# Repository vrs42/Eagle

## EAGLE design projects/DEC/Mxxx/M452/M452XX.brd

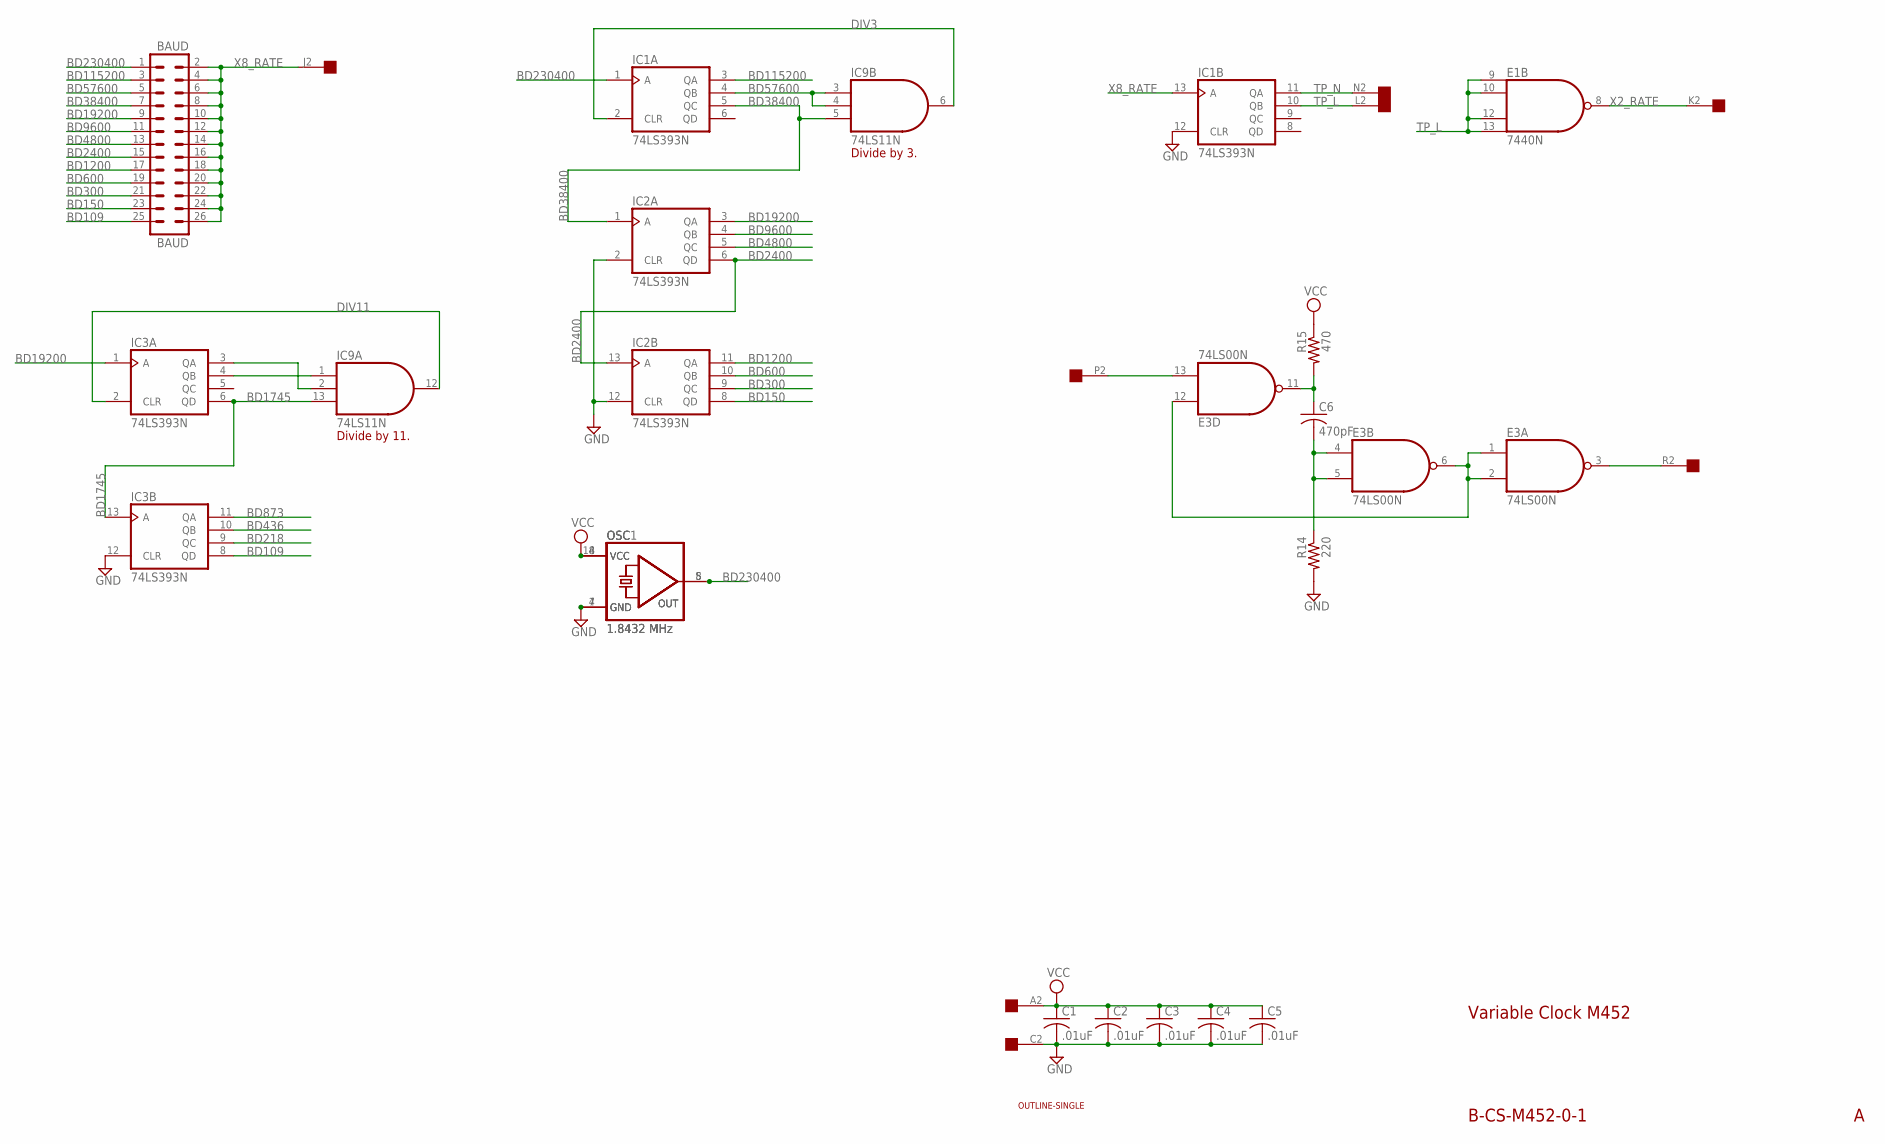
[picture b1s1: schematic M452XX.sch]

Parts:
BAUD: BAUD; MA13-2
C1, C2, C3, C4, C5: .01uF; C050-025X075
C6: 470pF; C150-054X183
E1: 7440N; DIL14
E3: 74LS00N; DIL14
IC1, IC2, IC3: 74LS393N; DIL14
IC9: 74LS11N; DIL14
OSC: 1.8432 MHz; DIL08S
OSC1: 1.8432 MHz; DIL14S
R14: 220; 0207/10
R15: 470; 0207/10
U$1: OUTLINE-SINGLE; SINGLE
U$2: EDGE-1; EDGE-CON1

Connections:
BD109: BAUD.25, IC3.8 (QD)
BD150: BAUD.23, IC2.8 (QD)
BD218: IC3.9 (QC)
BD300: BAUD.21, IC2.9 (QC)
BD436: IC3.10 (QB)
BD600: BAUD.19, IC2.10 (QB)
BD873: IC3.11 (QA)
BD1200: BAUD.17, IC2.11 (QA)
BD1745: IC3.6 (QD), IC3.13 (A), IC9.13 (I2)
BD2400: BAUD.15, IC2.6 (QD), IC2.13 (A)
BD4800: BAUD.13, IC2.5 (QC)
BD9600: BAUD.11, IC2.4 (QB)
BD19200: BAUD.9, IC2.3 (QA), IC3.1 (A)
BD38400: BAUD.7, IC1.5 (QC), IC2.1 (A), IC9.5 (I2)
BD57600: BAUD.5, IC1.4 (QB), IC9.3 (I0), IC9.4 (I1)
BD115200: BAUD.3, IC1.3 (QA)
BD230400: BAUD.1, IC1.1 (A), OSC.5 (OUT), OSC1.8 (OUT)
DIV3: IC1.2 (CLR), IC9.6 (O)
DIV11: IC3.2 (CLR), IC9.12 (O)
GND: C1.2, C2.2, C3.2, C4.2, C5.2, E1.7 (GND), E3.7 (GND), IC1.7 (GND), IC1.12 (CLR), IC2.2 (CLR), IC2.7 (GND), IC2.12 (CLR), IC3.7 (GND), IC3.12 (CLR), IC9.7 (GND), OSC.4 (GND), OSC1.7 (GND), R14.2, U$2.C2
unnamed: E3.13 (I1), U$2.P2
unnamed: C6.2, E3.4 (I0), E3.5 (I1), R14.1
unnamed: C6.1, E3.11 (O), R15.2
unnamed: E3.1 (I0), E3.2 (I1), E3.6 (O), E3.12 (I0)
unnamed: E3.3 (O), U$2.R2
unnamed: IC3.3 (QA), IC9.2 (I1)
unnamed: IC3.4 (QB), IC9.1 (I0)
TP_L: E1.9 (I0), E1.10 (I1), E1.12 (I2), E1.13 (I3), IC1.10 (QB), U$2.L2
TP_N: IC1.11 (QA), U$2.N2
VCC: C1.1, C2.1, C3.1, C4.1, C5.1, E1.14 (VCC), E3.14 (VCC), IC1.14 (VCC), IC2.14 (VCC), IC3.14 (VCC), IC9.14 (VCC), OSC.8 (VCC), OSC1.14 (VCC), R15.1, U$2.A2
X2_RATE: E1.8 (O), U$2.K2
X8_RATE: BAUD.2, BAUD.4, BAUD.6, BAUD.8, BAUD.10, BAUD.12, BAUD.14, BAUD.16, BAUD.18, BAUD.20, BAUD.22, BAUD.24, BAUD.26, IC1.13 (A), U$2.J2

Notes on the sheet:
Variable Clock M452
B-CS-M452-0-1
Divide by 11.
Divide by 3.

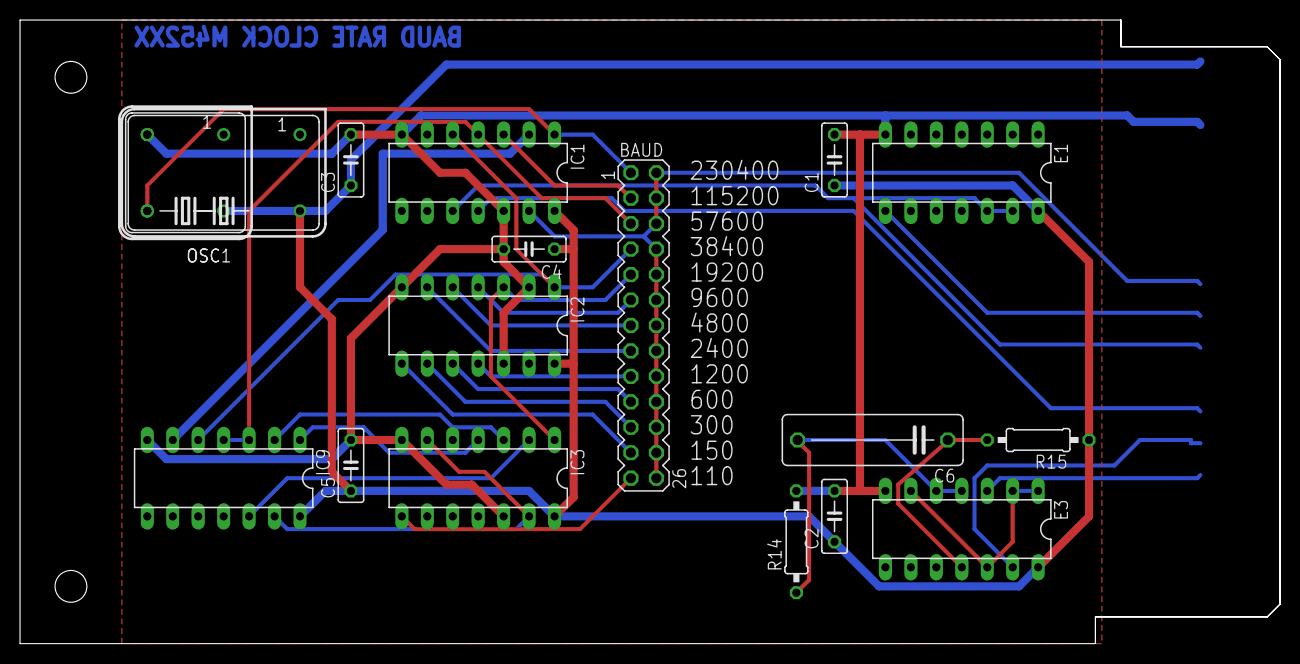
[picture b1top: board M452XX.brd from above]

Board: 2 copper layers, 125.7 x 62.2 mm, 19 parts (0 on the bottom side), 29 nets.

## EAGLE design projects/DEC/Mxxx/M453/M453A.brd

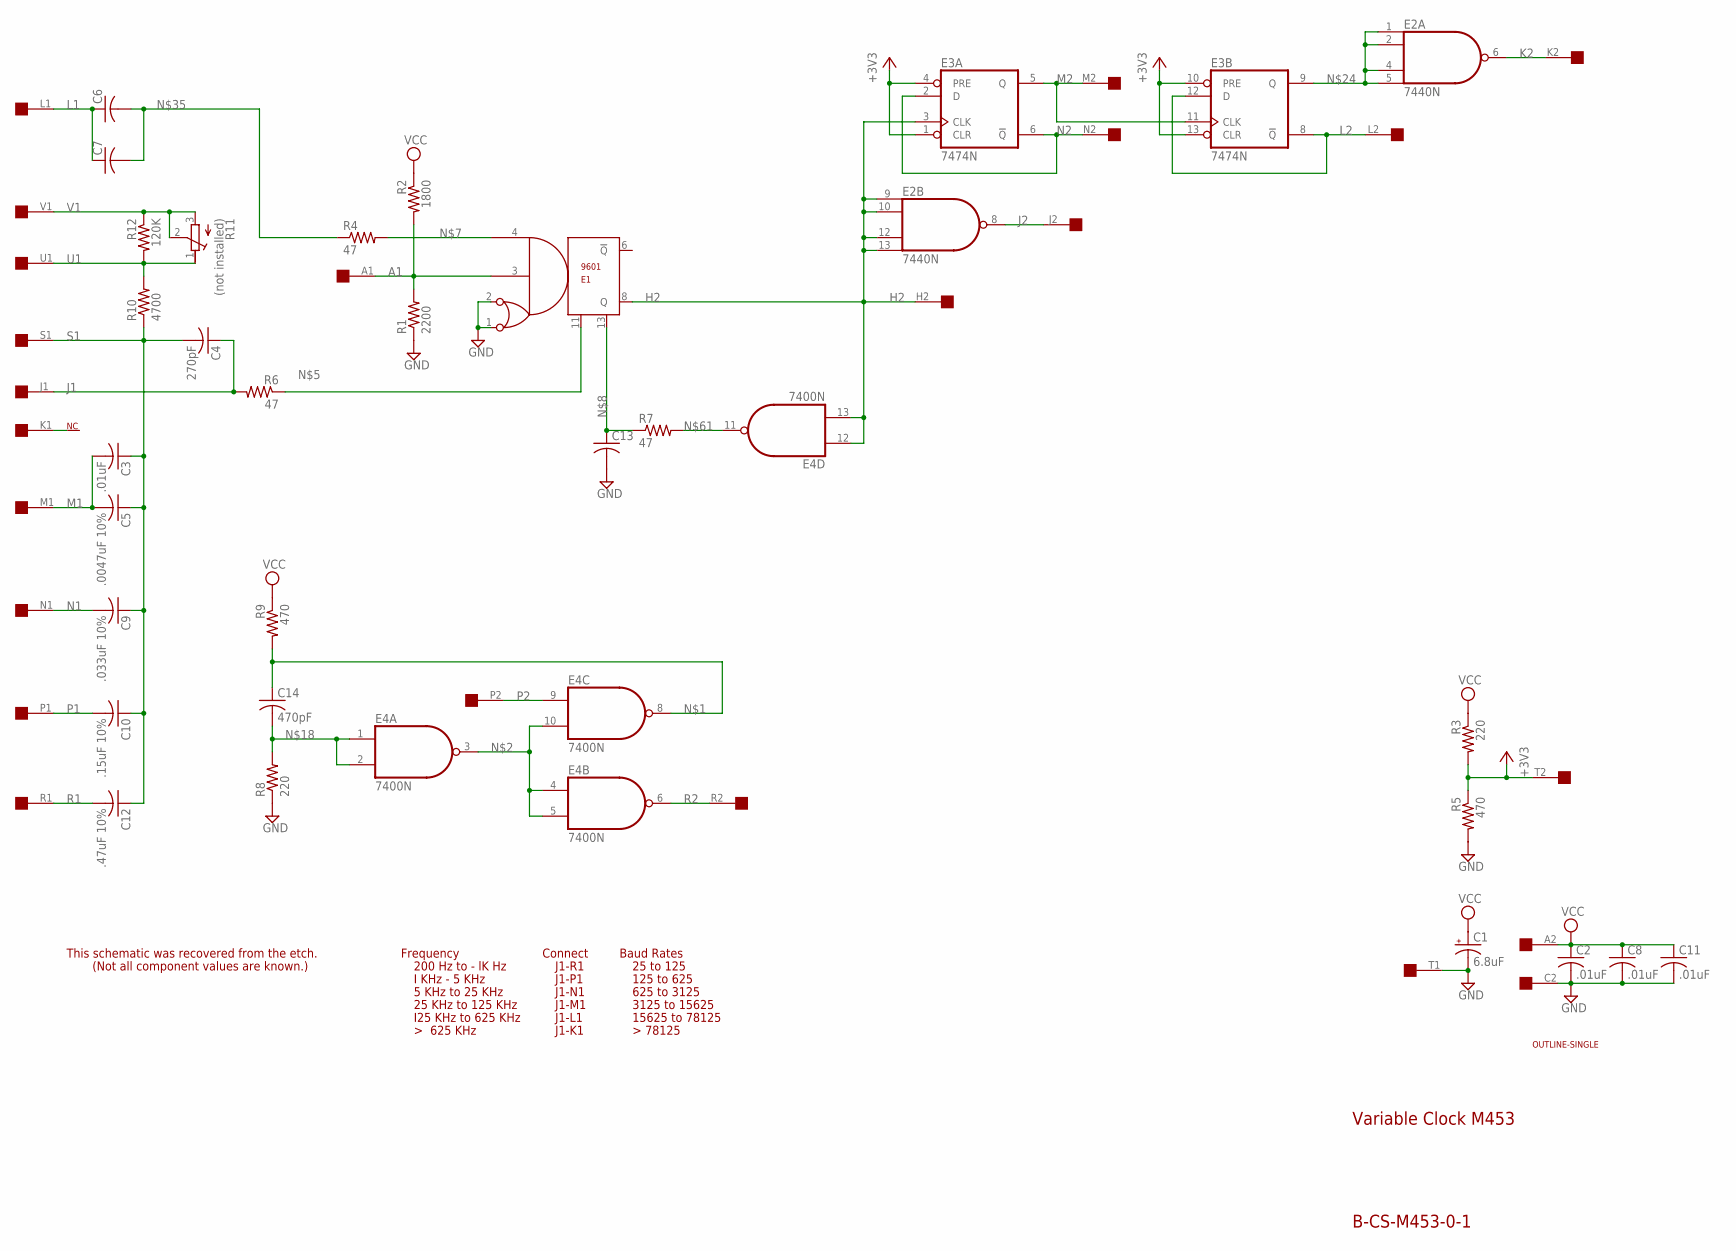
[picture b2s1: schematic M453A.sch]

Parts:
C1: 6.8uF; E12-8
C2, C3, C8, C11: .01uF; C050-025X075
C4: 270pF; C050-025X075
C5: .0047uF 10%; C225-062X268
C6, C7, C13: C-US050-025X075; C050-025X075
C9: .033uF 10%; C225-062X268
C10: .15uF 10%; C325-137X374
C12: .47uF 10%; C375-155X418
C14: 470pF; C050-025X075
E1: 9601; DIL14
E2: 7440N; DIL14
E3: 7474N; DIL14
E4: 7400N; DIL14
R1: 2200; 0207/10
R2: 1800; 0207/10
R3, R8: 220; 0207/10
R4, R6, R7: 47; 0207/10
R5, R9: 470; 0207/10
R10: 4700; 0207/10
R11: (not installed); 3006Y
R12: 120K; 0207/10
U$1: OUTLINE-SINGLE; SINGLE
U$3: SINGLE; EDGE-CON2

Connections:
+3V3: E3.1 (CLR), E3.4 (PRE), E3.10 (PRE), E3.13 (CLR), R3.2, R5.1, U$3.T2
A1: E1.3, R1.2, R2.2, U$3.A1
GND: C1.-, C2.2, C8.2, C11.2, C13.2, E1.1, E1.2, E1.7 (GND), E2.7 (GND), E3.7 (GND), E4.7 (GND), R1.1, R5.2, R8.1, U$3.C2, U$3.T1
H2: E1.8 (Q), E2.9 (I0), E2.10 (I1), E2.12 (I2), E2.13 (I3), E3.3 (CLK), E4.12 (I0), E4.13 (I1), U$3.H2
J1: C4.1, R6.2, U$3.J1
J2: E2.8 (O), U$3.J2
K2: E2.6 (O), U$3.K2
L1: C6.1, C7.1, U$3.L1
L2: E3.8 (!Q), E3.12 (D), U$3.L2
M1: C3.2, C5.2, U$3.M1
M2: E3.5 (Q), E3.11 (CLK), U$3.M2
N1: C9.2, U$3.N1
N2: E3.2 (D), E3.6 (!Q), U$3.N2
unnamed: C14.1, E4.8 (O), R9.2
unnamed: E4.3 (O), E4.4 (I0), E4.5 (I1), E4.10 (I1)
unnamed: E1.11, R6.1
unnamed: E1.4, R4.2
unnamed: C13.1, E1.13, R7.1
unnamed: C14.2, E4.1 (I0), E4.2 (I1), R8.2
unnamed: E2.1 (I0), E2.2 (I1), E2.4 (I2), E2.5 (I3), E3.9 (Q)
unnamed: C6.2, C7.2, R4.1
unnamed: E4.11 (O), R7.2
NC: U$3.K1
P1: C10.2, U$3.P1
P2: E4.9 (I0), U$3.P2
R1: C12.2, U$3.R1
R2: E4.6 (O), U$3.R2
S1: C3.1, C4.2, C5.1, C9.1, C10.1, C12.1, R10.1, U$3.S1
U1: R10.2, R11.1 (A), R12.2, U$3.U1
V1: R11.2 (S), R11.3 (E), R12.1, U$3.V1
VCC: C1.+, C2.1, C8.1, C11.1, E1.14 (VCC), E2.14 (VCC), E3.14 (VCC), E4.14 (VCC), R2.1, R3.1, R9.1, U$3.A2

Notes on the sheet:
Variable Clock M453
B-CS-M453-0-1
This schematic was recovered from the etch.
(Not all component values are known.)
Frequency
200 Hz to - lK Hz
I KHz - 5 KHz
5 KHz to 25 KHz
25 KHz to 125 KHz
I25 KHz to 625 KHz
Connect
J1-R1
J1-P1
J1-N1
J1-M1
J1-L1
J1-K1
Baud Rates
25 to 125
125 to 625
625 to 3125
3125 to 15625
15625 to 78125

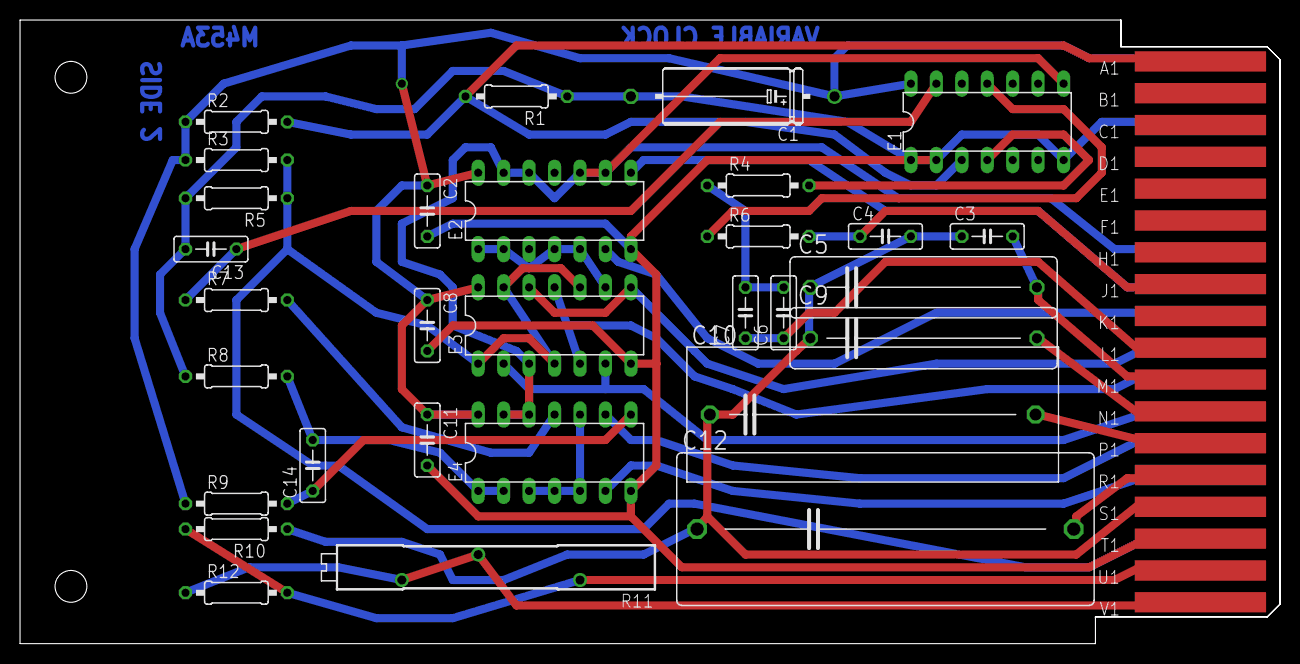
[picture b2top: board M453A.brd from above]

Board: 2 copper layers, 125.7 x 62.2 mm, 32 parts (0 on the bottom side), 30 nets.

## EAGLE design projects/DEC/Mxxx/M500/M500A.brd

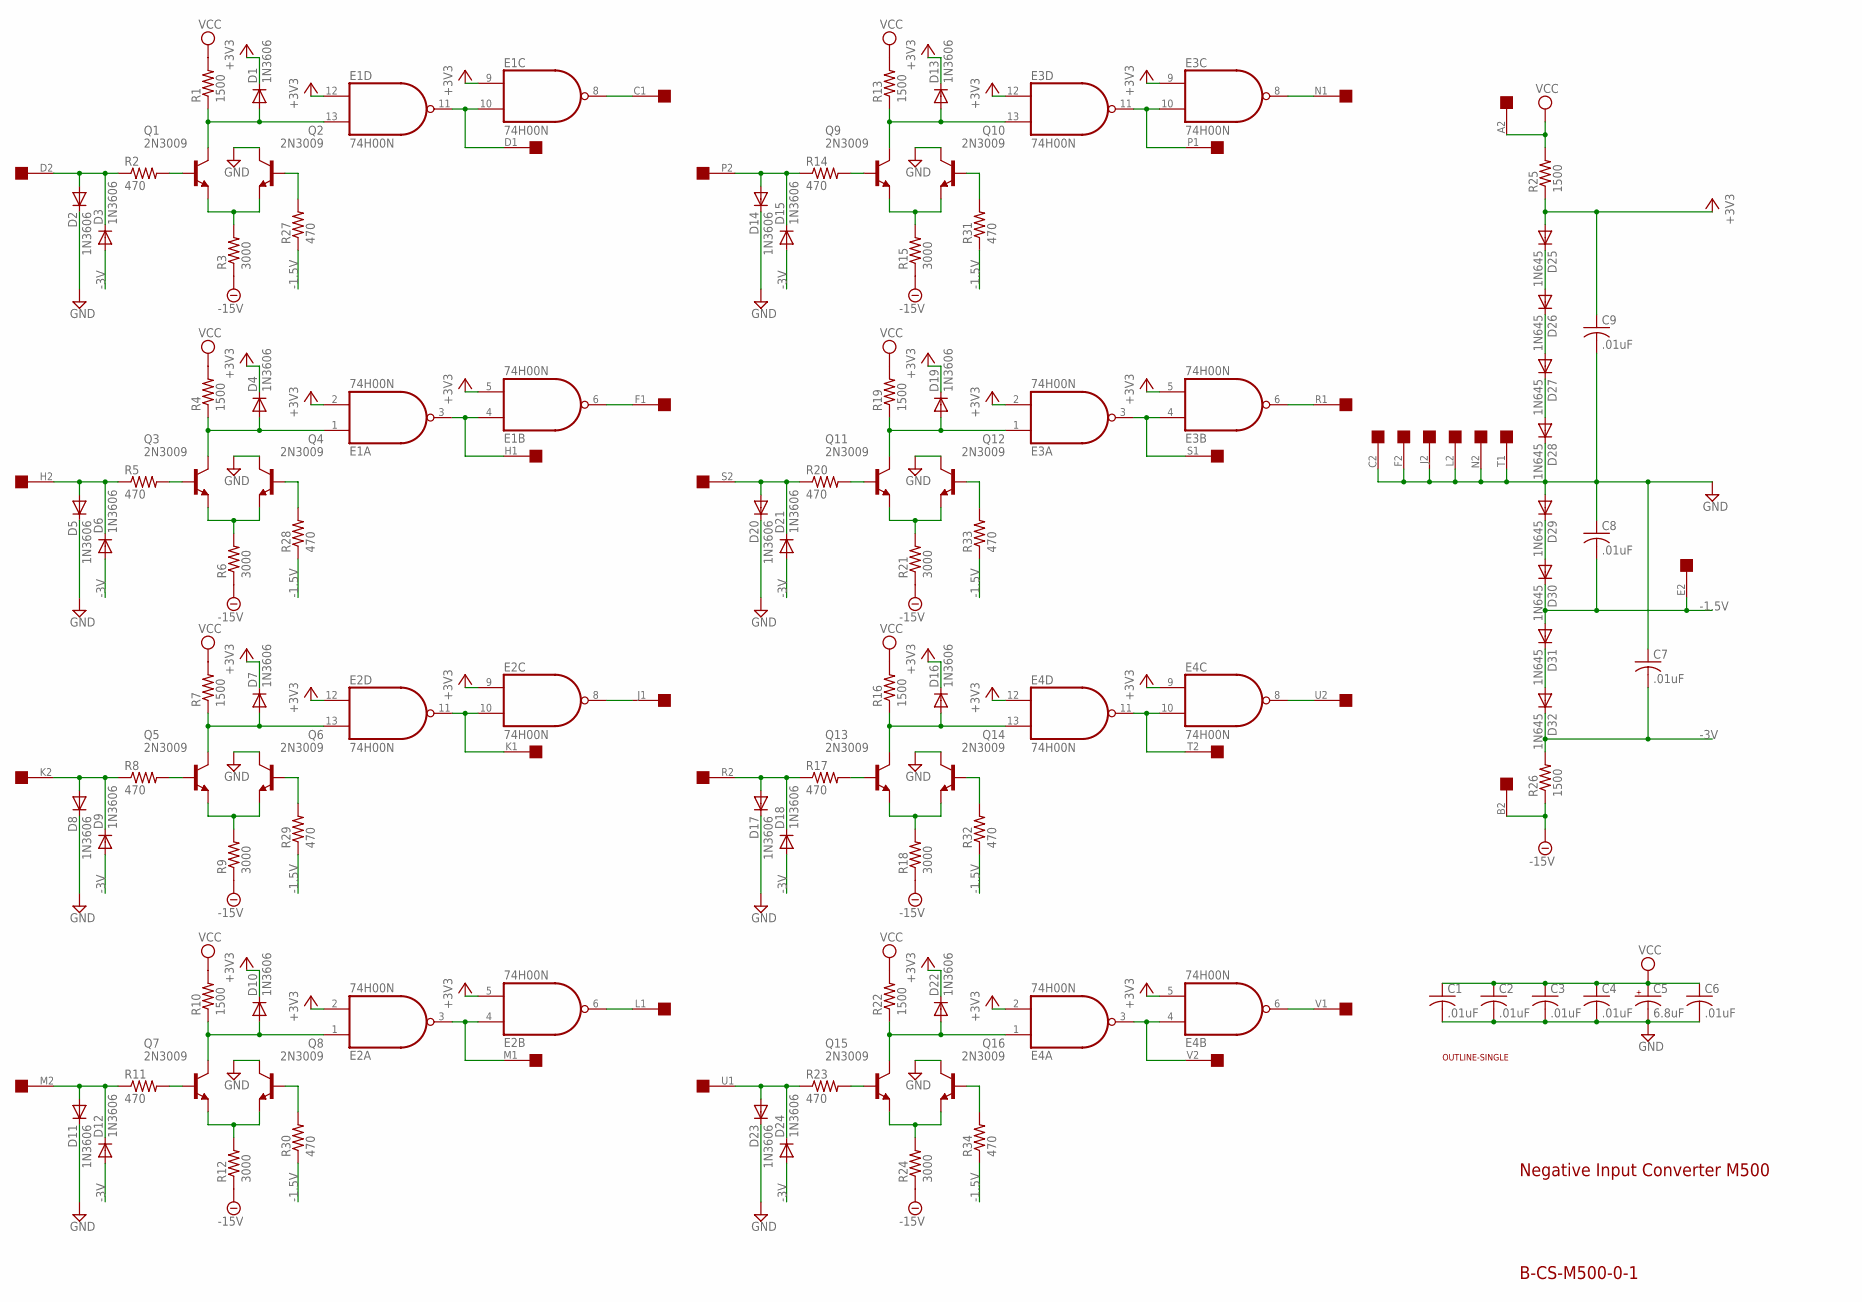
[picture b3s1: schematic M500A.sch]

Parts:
C1, C2, C3, C4, C6, C7, C8, C9: .01uF; C050-025X075
C5: 6.8uF; E12-8
D1, D2, D3, D4, D5, D6, D7, D8, D9, D10, D11, D12, D13, D14, D15, D16, D17, D18, D19, D20, D21, D22, D23, D24: 1N3606; DO35-10
D25, D26, D27, D28, D29, D30, D31, D32: 1N645; DO35-10
E1, E2, E3, E4: 74H00N; DIL14
Q1, Q2, Q3, Q4, Q5, Q6, Q7, Q8, Q9, Q10, Q11, Q12, Q13, Q14, Q15, Q16: 2N3009; TO39
R1, R4, R7, R10, R13, R16, R19, R22, R25, R26: 1500; 0207/10
R2, R5, R8, R11, R14, R17, R20, R23, R27, R28, R29, R30, R31, R32, R33, R34: 470; 0207/10
R3, R6, R9, R12, R15, R18, R21, R24: 3000; 0207/10
U$1: OUTLINE-SINGLE; SINGLE
U$3: SINGLE; EDGE-CON2

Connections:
+3V3: C9.1, D1.C, D4.C, D7.C, D10.C, D13.C, D16.C, D19.C, D22.C, D25.A, E1.2 (I1), E1.5 (I1), E1.9 (I0), E1.12 (I0), E2.2 (I1), E2.5 (I1), E2.9 (I0), E2.12 (I0), E3.2 (I1), E3.5 (I1), E3.9 (I0), E3.12 (I0), E4.2 (I1), E4.5 (I1), E4.9 (I0), E4.12 (I0), R25.1
-1.5V: C8.2, D30.C, D31.A, R27.1, R28.1, R29.1, R30.1, R31.1, R32.1, R33.1, R34.1, U$3.E2
-3V: C7.2, D3.A, D6.A, D9.A, D12.A, D15.A, D18.A, D21.A, D24.A, D32.C, R26.2
-15V: R3.1, R6.1, R9.1, R12.1, R15.1, R18.1, R21.1, R24.1, R26.1, U$3.B2
GND: C1.2, C2.2, C3.2, C4.2, C5.-, C6.2, C7.1, C8.1, C9.2, D2.C, D5.C, D8.C, D11.C, D14.C, D17.C, D20.C, D23.C, D28.C, D29.A, E1.7 (GND), E2.7 (GND), E3.7 (GND), E4.7 (GND), Q2.3 (C), Q4.3 (C), Q6.3 (C), Q8.3 (C), Q10.3 (C), Q12.3 (C), Q14.3 (C), Q16.3 (C), U$3.C2, U$3.F2, U$3.J2, U$3.L2, U$3.N2, U$3.T1
unnamed: E1.10 (I1), E1.11 (O), U$3.D1
unnamed: E1.8 (O), U$3.C1
unnamed: Q1.1 (E), Q2.1 (E), R3.2
unnamed: D1.A, E1.13 (I1), Q1.3 (C), R1.1
unnamed: Q1.2 (B), R2.2
unnamed: D2.A, D3.C, R2.1, U$3.D2
unnamed: Q2.2 (B), R27.2
unnamed: E1.3 (O), E1.4 (I0), U$3.H1
unnamed: E1.6 (O), U$3.F1
unnamed: Q3.1 (E), Q4.1 (E), R6.2
unnamed: D4.A, E1.1 (I0), Q3.3 (C), R4.1
unnamed: Q3.2 (B), R5.2
unnamed: D5.A, D6.C, R5.1, U$3.H2
unnamed: D27.C, D28.A
unnamed: Q4.2 (B), R28.2
unnamed: E2.10 (I1), E2.11 (O), U$3.K1
unnamed: E2.8 (O), U$3.J1
unnamed: Q5.1 (E), Q6.1 (E), R9.2
unnamed: D7.A, E2.13 (I1), Q5.3 (C), R7.1
unnamed: Q5.2 (B), R8.2
unnamed: D8.A, D9.C, R8.1, U$3.K2
unnamed: D26.C, D27.A
unnamed: Q6.2 (B), R29.2
unnamed: E2.3 (O), E2.4 (I0), U$3.M1
unnamed: E2.6 (O), U$3.L1
unnamed: Q7.1 (E), Q8.1 (E), R12.2
unnamed: D10.A, E2.1 (I0), Q7.3 (C), R10.1
unnamed: Q7.2 (B), R11.2
unnamed: D11.A, D12.C, R11.1, U$3.M2
unnamed: D25.C, D26.A
unnamed: Q8.2 (B), R30.2
unnamed: E3.10 (I1), E3.11 (O), U$3.P1
unnamed: E3.8 (O), U$3.N1
unnamed: Q9.1 (E), Q10.1 (E), R15.2
unnamed: D13.A, E3.13 (I1), Q9.3 (C), R13.1
unnamed: Q9.2 (B), R14.2
unnamed: D14.A, D15.C, R14.1, U$3.P2
unnamed: D29.C, D30.A
unnamed: Q10.2 (B), R31.2
unnamed: E3.3 (O), E3.4 (I0), U$3.S1
unnamed: E3.6 (O), U$3.R1
unnamed: Q11.1 (E), Q12.1 (E), R21.2
unnamed: D19.A, E3.1 (I0), Q11.3 (C), R19.1
unnamed: Q11.2 (B), R20.2
unnamed: D20.A, D21.C, R20.1, U$3.S2
unnamed: D31.C, D32.A
unnamed: Q12.2 (B), R33.2
unnamed: E4.10 (I1), E4.11 (O), U$3.T2
unnamed: E4.8 (O), U$3.U2
unnamed: Q13.1 (E), Q14.1 (E), R18.2
unnamed: D16.A, E4.13 (I1), Q13.3 (C), R16.1
unnamed: Q13.2 (B), R17.2
unnamed: D17.A, D18.C, R17.1, U$3.R2
unnamed: Q14.2 (B), R32.2
unnamed: E4.3 (O), E4.4 (I0), U$3.V2
unnamed: E4.6 (O), U$3.V1
unnamed: Q15.1 (E), Q16.1 (E), R24.2
unnamed: D22.A, E4.1 (I0), Q15.3 (C), R22.1
unnamed: Q15.2 (B), R23.2
unnamed: D23.A, D24.C, R23.1, U$3.U1
unnamed: Q16.2 (B), R34.2
VCC: C1.1, C2.1, C3.1, C4.1, C5.+, C6.1, E1.14 (VCC), E2.14 (VCC), E3.14 (VCC), E4.14 (VCC), R1.2, R4.2, R7.2, R10.2, R13.2, R16.2, R19.2, R22.2, R25.2, U$3.A2

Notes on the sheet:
Negative Input Converter M500
B-CS-M500-0-1

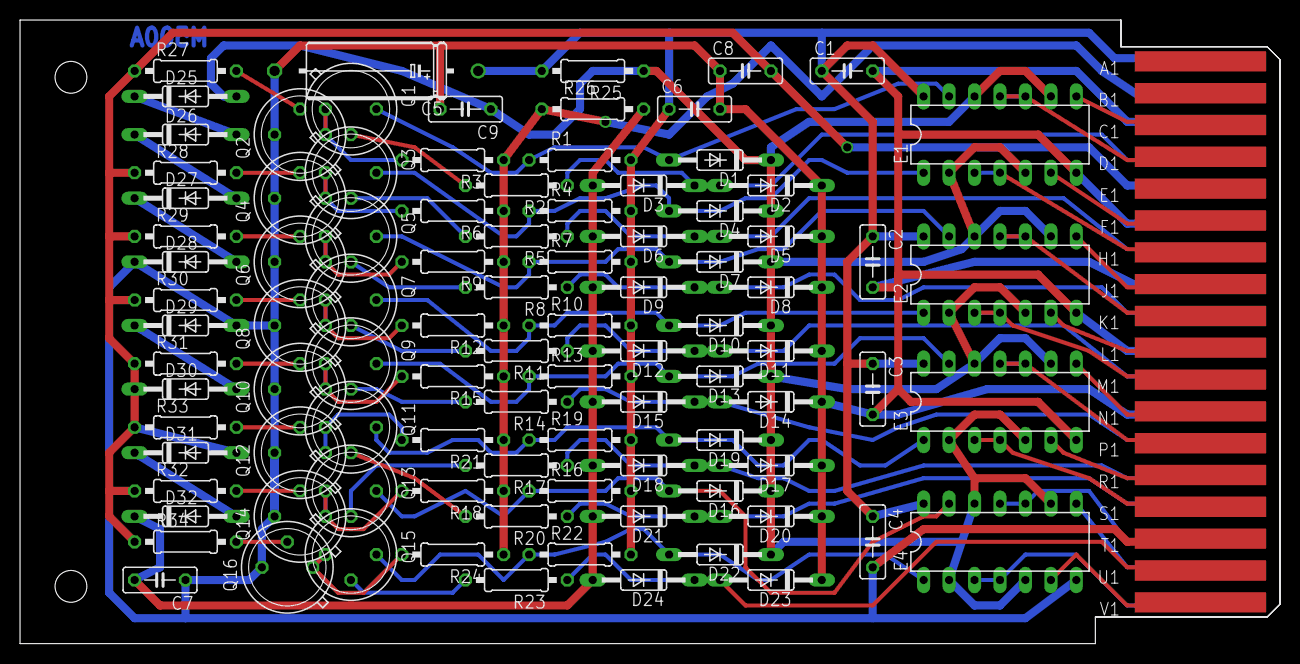
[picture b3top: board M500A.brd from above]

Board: 2 copper layers, 125.7 x 62.2 mm, 97 parts (0 on the bottom side), 67 nets.

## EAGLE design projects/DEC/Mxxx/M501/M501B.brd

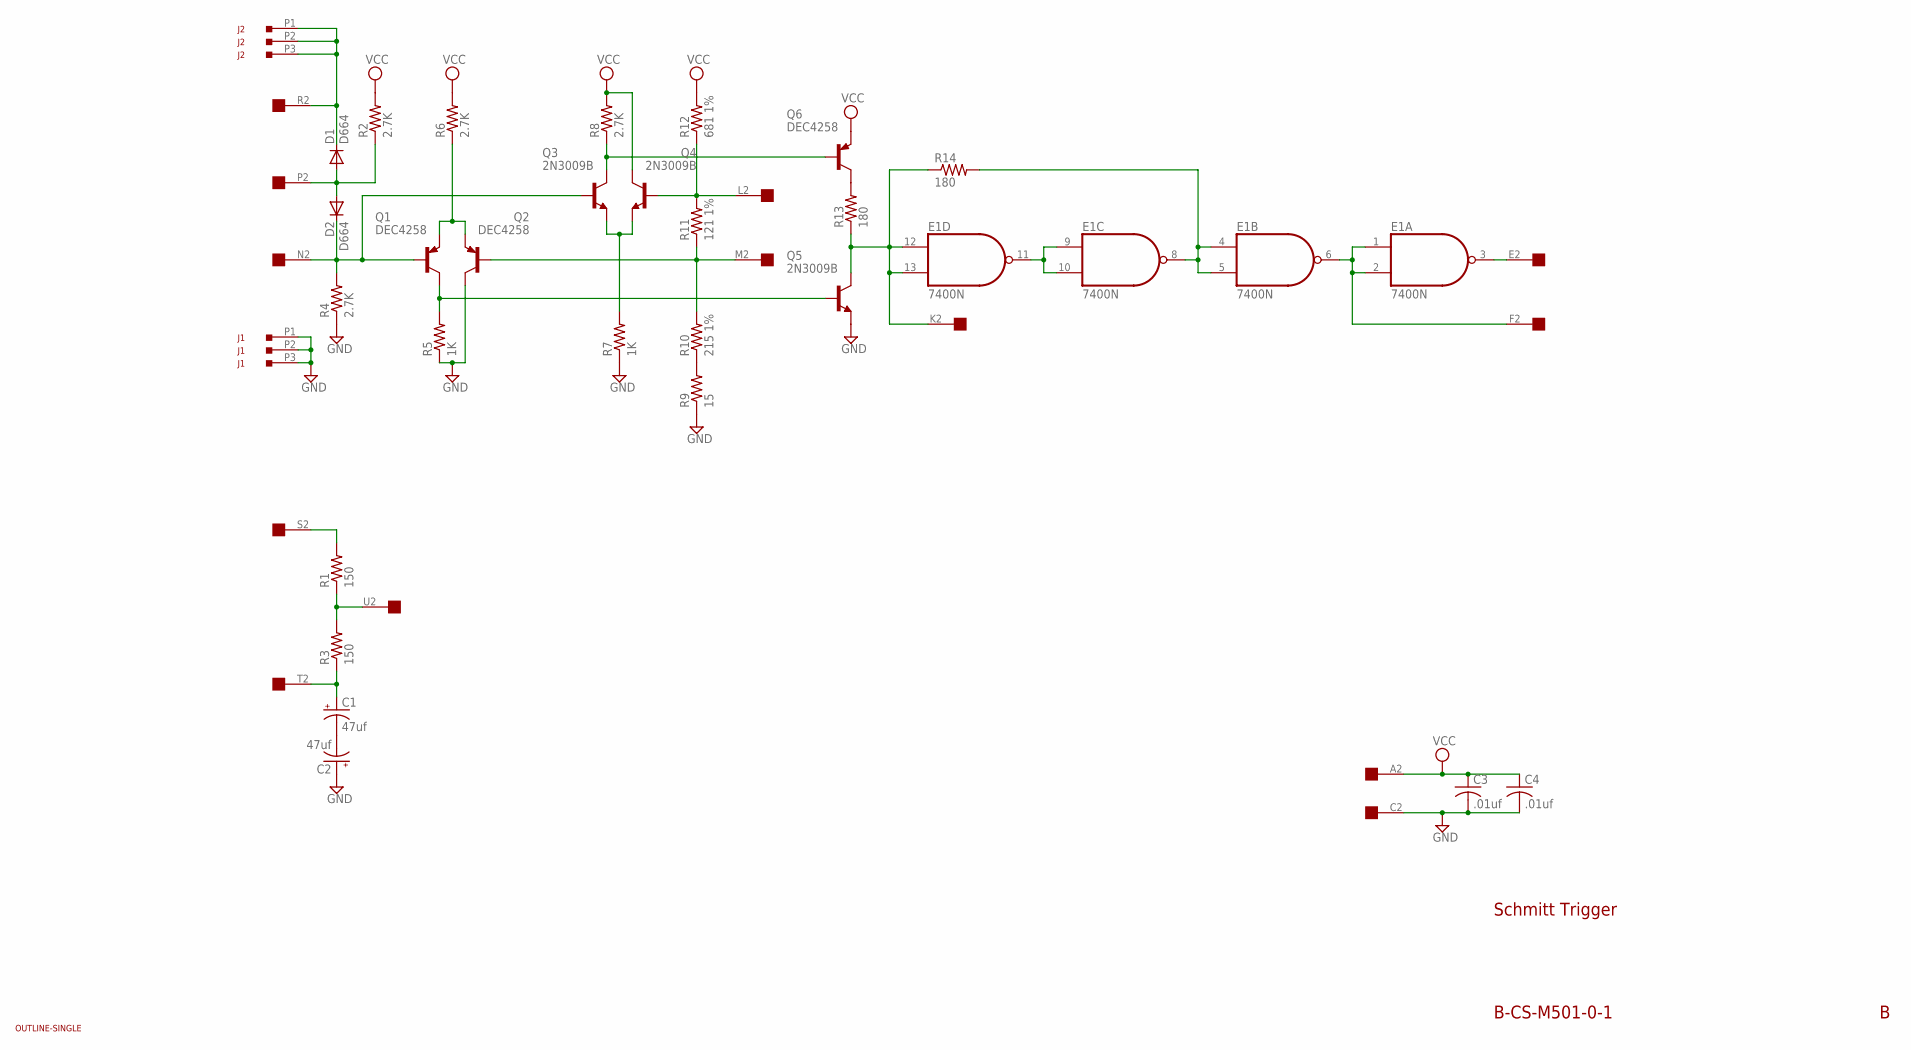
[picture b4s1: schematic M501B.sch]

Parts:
C1, C2: 47uf; E22-6
C3, C4: .01uf; C075-032X103
D1, D2: D664; DO35-10
E1: 7400N; DIL14
J1, J2: 34-22-1-03
Q1, Q2, Q6: DEC4258; TO39
Q3, Q4, Q5: 2N3009B; TO39
R1, R3: 150; 0207/10
R2, R4, R6, R8: 2.7K; 0207/10
R5, R7: 1K; 0207/10
R9: 15; 0207/10
R10: 215 1%; 0207/15
R11: 121 1%; 0207/15
R12: 681 1%; 0207/15
R13, R14: 180; 0207/10
U$1: EDGE-1; EDGE-CON1
U$4: OUTLINE-SINGLE; SINGLE

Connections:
E: E1.3 (O), U$1.E2
F: E1.1 (I0), E1.2 (I1), E1.6 (O), U$1.F2
GND: C2.+, C3.2, C4.2, E1.7 (GND), J1.P1, J1.P2, J1.P3, Q2.3 (C), Q5.1 (E), R4.1, R5.1, R7.1, R9.1, U$1.C2
K: E1.12 (I0), E1.13 (I1), Q5.3 (C), R13.1, R14.1, U$1.K2
L: Q4.2 (B), R11.2, R12.1, U$1.L2
M: Q2.2 (B), R10.2, R11.1, U$1.M2
N: D2.C, Q1.2 (B), Q3.2 (B), R4.2, U$1.N2
unnamed: E1.9 (I0), E1.10 (I1), E1.11 (O)
unnamed: E1.4 (I0), E1.5 (I1), E1.8 (O), R14.2
unnamed: R1.2, U$1.S2
unnamed: R1.1, R3.2, U$1.U2
unnamed: C1.+, R3.1, U$1.T2
unnamed: C1.-, C2.-
unnamed: Q1.1 (E), Q2.1 (E), R6.1
unnamed: Q1.3 (C), Q5.2 (B), R5.2
unnamed: Q3.1 (E), Q4.1 (E), R7.2
unnamed: R9.2, R10.1
unnamed: Q3.3 (C), Q6.2 (B), R8.1
unnamed: Q6.3 (C), R13.2
P: D1.A, D2.A, R2.1, U$1.P2
R: D1.C, J2.P1, J2.P2, J2.P3, U$1.R2
VCC: C3.1, C4.1, E1.14 (VCC), Q4.3 (C), Q6.1 (E), R2.2, R6.2, R8.2, R12.2, U$1.A2

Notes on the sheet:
Schmitt Trigger
B-CS-M501-0-1

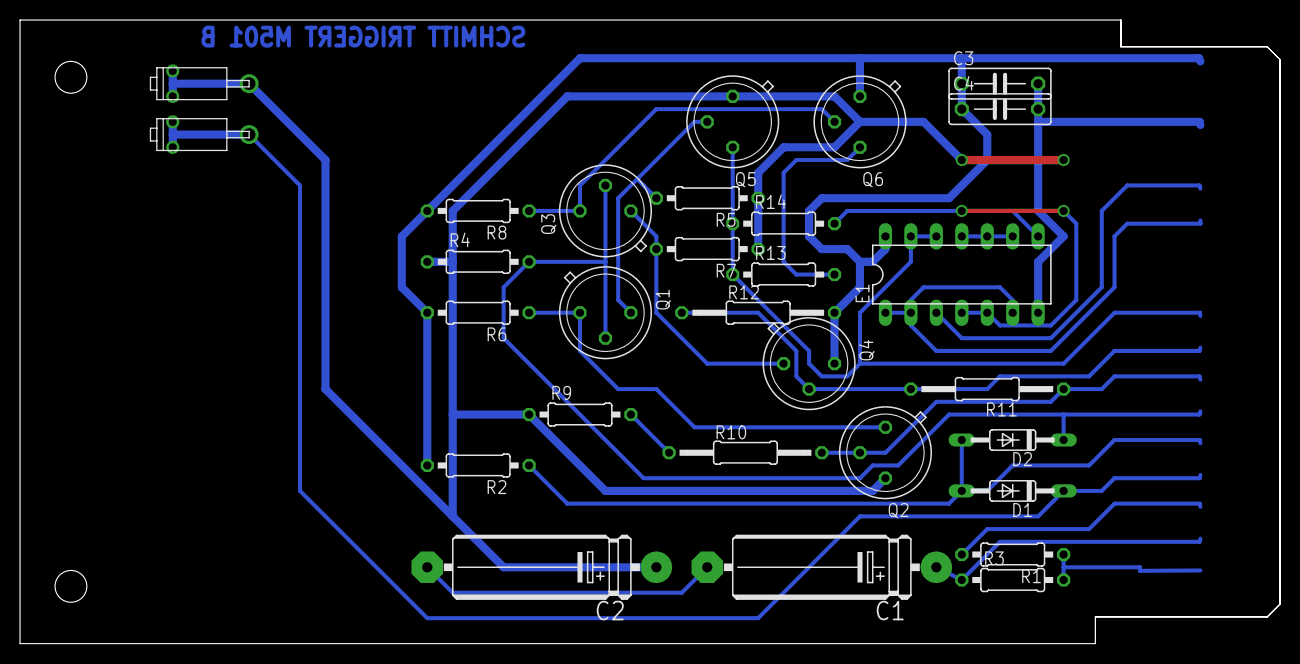
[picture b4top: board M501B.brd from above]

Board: 2 copper layers, 125.7 x 62.2 mm, 31 parts (0 on the bottom side), 22 nets.
